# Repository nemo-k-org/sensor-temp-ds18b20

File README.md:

# Nemo-K temperature sensor for DS18B20

## Overview

This is Nemo-K board for ESP-01 and well-known [DS18B20](https://www.analog.com/en/products/ds18b20.html) gauge.

Because of its measuring range (-55°C to +125°C, -67°F to +257°F) DS18B20 is ideal for all marine temperature
measurements e.g. salons, engine coolant, engine room. However, using this gauge for measuring except exhaust
pipe temperatures is out of its range.

The board is designed to be used with ESP-01 microcontroller running Nemo-K firmware.

## Content

The repository contains schematics and PCB in KiCad 8.0 format. The footprint properties contains LCSC part numbers
used by [JLCPBC.com](https://jlcpcb.com). If present, the `sensor-temp-ds18b20/production/` contains all necessary
files to order boards from JLCPCB. The production files can be easily re-created using
[KiCad Fabrication Toolkit](https://github.com/bennymeg/Fabrication-Toolkit).

The Nemo-K project is not affiliated or sponsored by JLCPCB. The project does not endorse JLCPCB.

## Changelog

* *v2* First working version. The labels "Sens Data" and "Sens 3.3V" of the temperature sensor screw terminal
  are the wrong way around. A reverse polarity protection diode should be added.

## Copyright and License

The license and copyright can be found in the file `LICENSE`.

The license and copyright cover only the schematic diagram and the PCB design. It does not cover footprints and other
embedded elements or technical documentation which may or may not be covered by their own licenses.

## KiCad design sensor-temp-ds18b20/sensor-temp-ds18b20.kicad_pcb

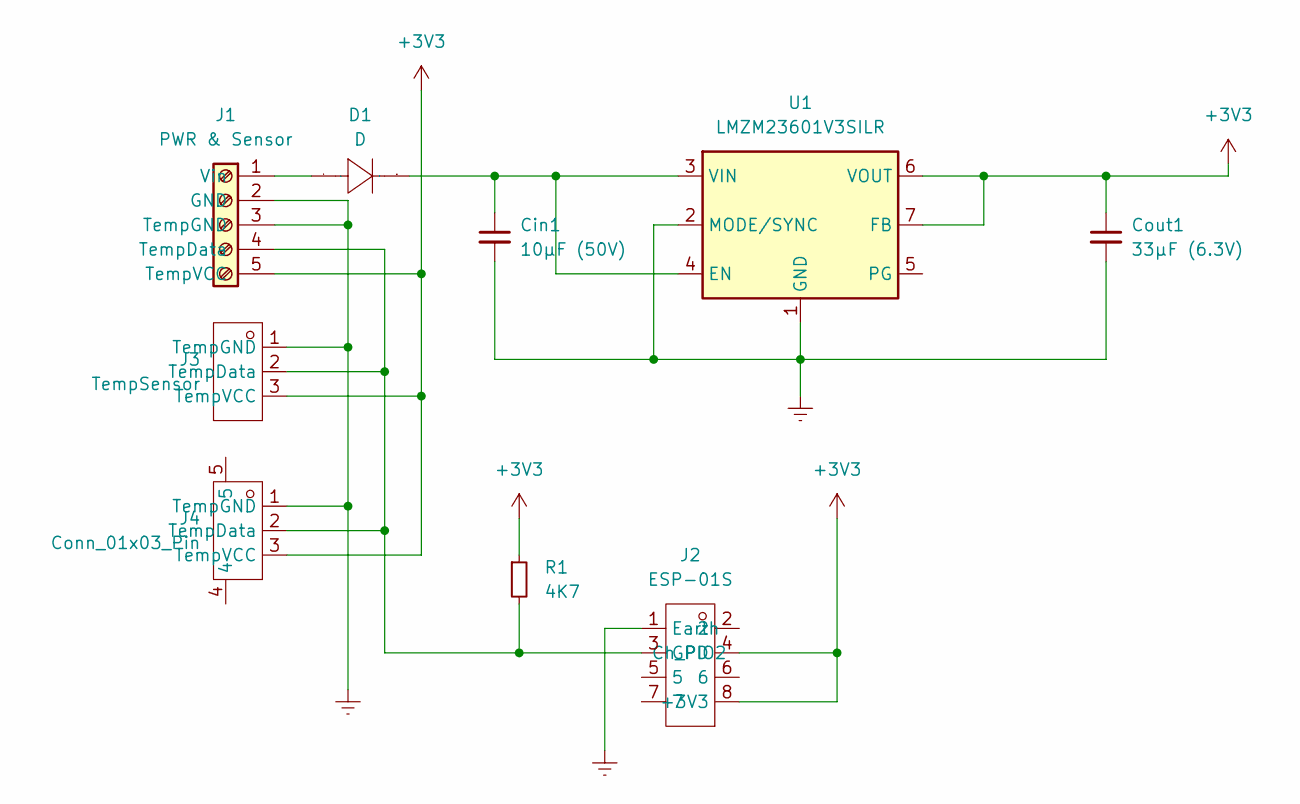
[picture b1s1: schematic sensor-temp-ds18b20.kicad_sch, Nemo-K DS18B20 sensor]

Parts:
Cin1: 10μF (50V); C_1210_3225Metric; LCSC C2918502
Cout1: 33μF (6.3V); C_1210_3225Metric; Mfg Part C3225X5R1A336MT0A0E; LCSC C531418
D1: D; SOD-323_L1.7-W1.3-LS2.5-RD; Manufacturer Part S7116-300A; LCSC Part Name S7116-300A
J1: PWR & Sensor; TerminalBlock_MetzConnect_Type086_RT03405HBLC_1x05_P3.81mm_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; MPN OSTOQ053251; LCSC C5349553
J2: ESP-01S; HDR-SMD_8P-P2.54-V-F-R2-C4-S7.1; Mfg Part PM254-2-04-S-8.5; LCSC C3975149
J3: TempSensor; HDR-TH_3P-P2.54_DZ254S-11-03-48; Manufacturer Part DZ254S-11-03-48; LCSC Part Name 间距:2.54mm 1x3P 立贴 方针
J4: Conn_01x03_Pin; CONN-SMD_3P-P2.50_SHOUHAN_2.54-3PWTDK; Manufacturer Part 2.54-3PWTDK; LCSC Part Name 1x3P 间距:2.5mm 卧贴
R1: 4K7; R_1206_3216Metric; LCSC C17936
U1: LMZM23601V3SILR; Texas_SIL0010A_MicroSiP-10-1EP_3.8x3mm_P0.6mm_EP0.7x2.9mm_T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; MPN LMZM23601SILR; LCSC C2864948

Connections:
+3V3: Cout1.1, J1.5 (TempVCC), J2.4 (Ch_PD), J2.8 (+3V3), J3.3 (TempVCC), J4.3 (TempVCC), R1.1, U1.6 (VOUT), U1.7 (FB)
Earth: Cin1.2, Cout1.2, J1.2 (GND), J1.3 (TempGND), J2.1 (Earth), J3.1 (TempGND), J4.1 (TempGND), U1.1 (GND), U1.2 (MODE/SYNC), U1.11 (GND)
unnamed: D1.2 (A), J1.1 (Vin)
unnamed: Cin1.1, D1.1 (K), U1.3 (VIN), U1.4 (EN)
unnamed: J1.4 (TempData), J2.3 (GPIO2), J3.2 (TempData), J4.2 (TempData), R1.2

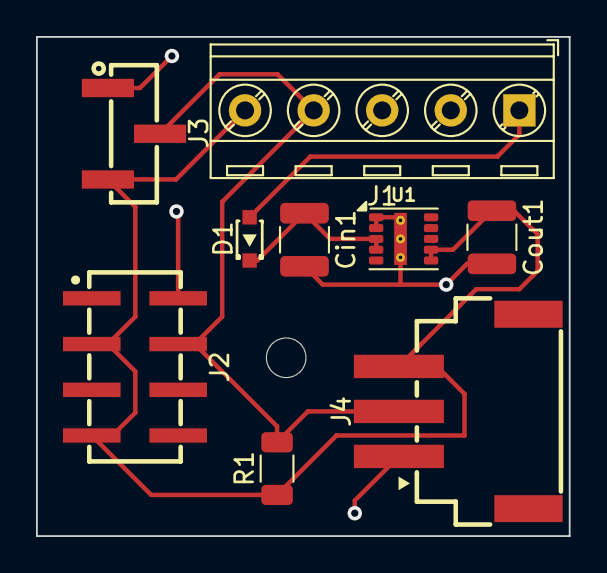
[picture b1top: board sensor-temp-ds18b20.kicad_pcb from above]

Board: 2 copper layers, 29.6 x 27.7 mm, 9 parts (0 on the bottom side), 5 nets.

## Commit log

2025-01-10 v2, the first working version
2025-01-10 Switch labels "Sens Data" and "Sens 3.3V" in the screw terminal J1
2025-01-10 Added reverse polarity protection and fixed the footprint paths
2025-01-14 Keep production files but no production file backups
